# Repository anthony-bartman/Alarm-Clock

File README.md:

# Alarm-Clock
Using Fusion360 and Eagle, I designed an alarm clock circuit board from scratch in my embedded fabrication class

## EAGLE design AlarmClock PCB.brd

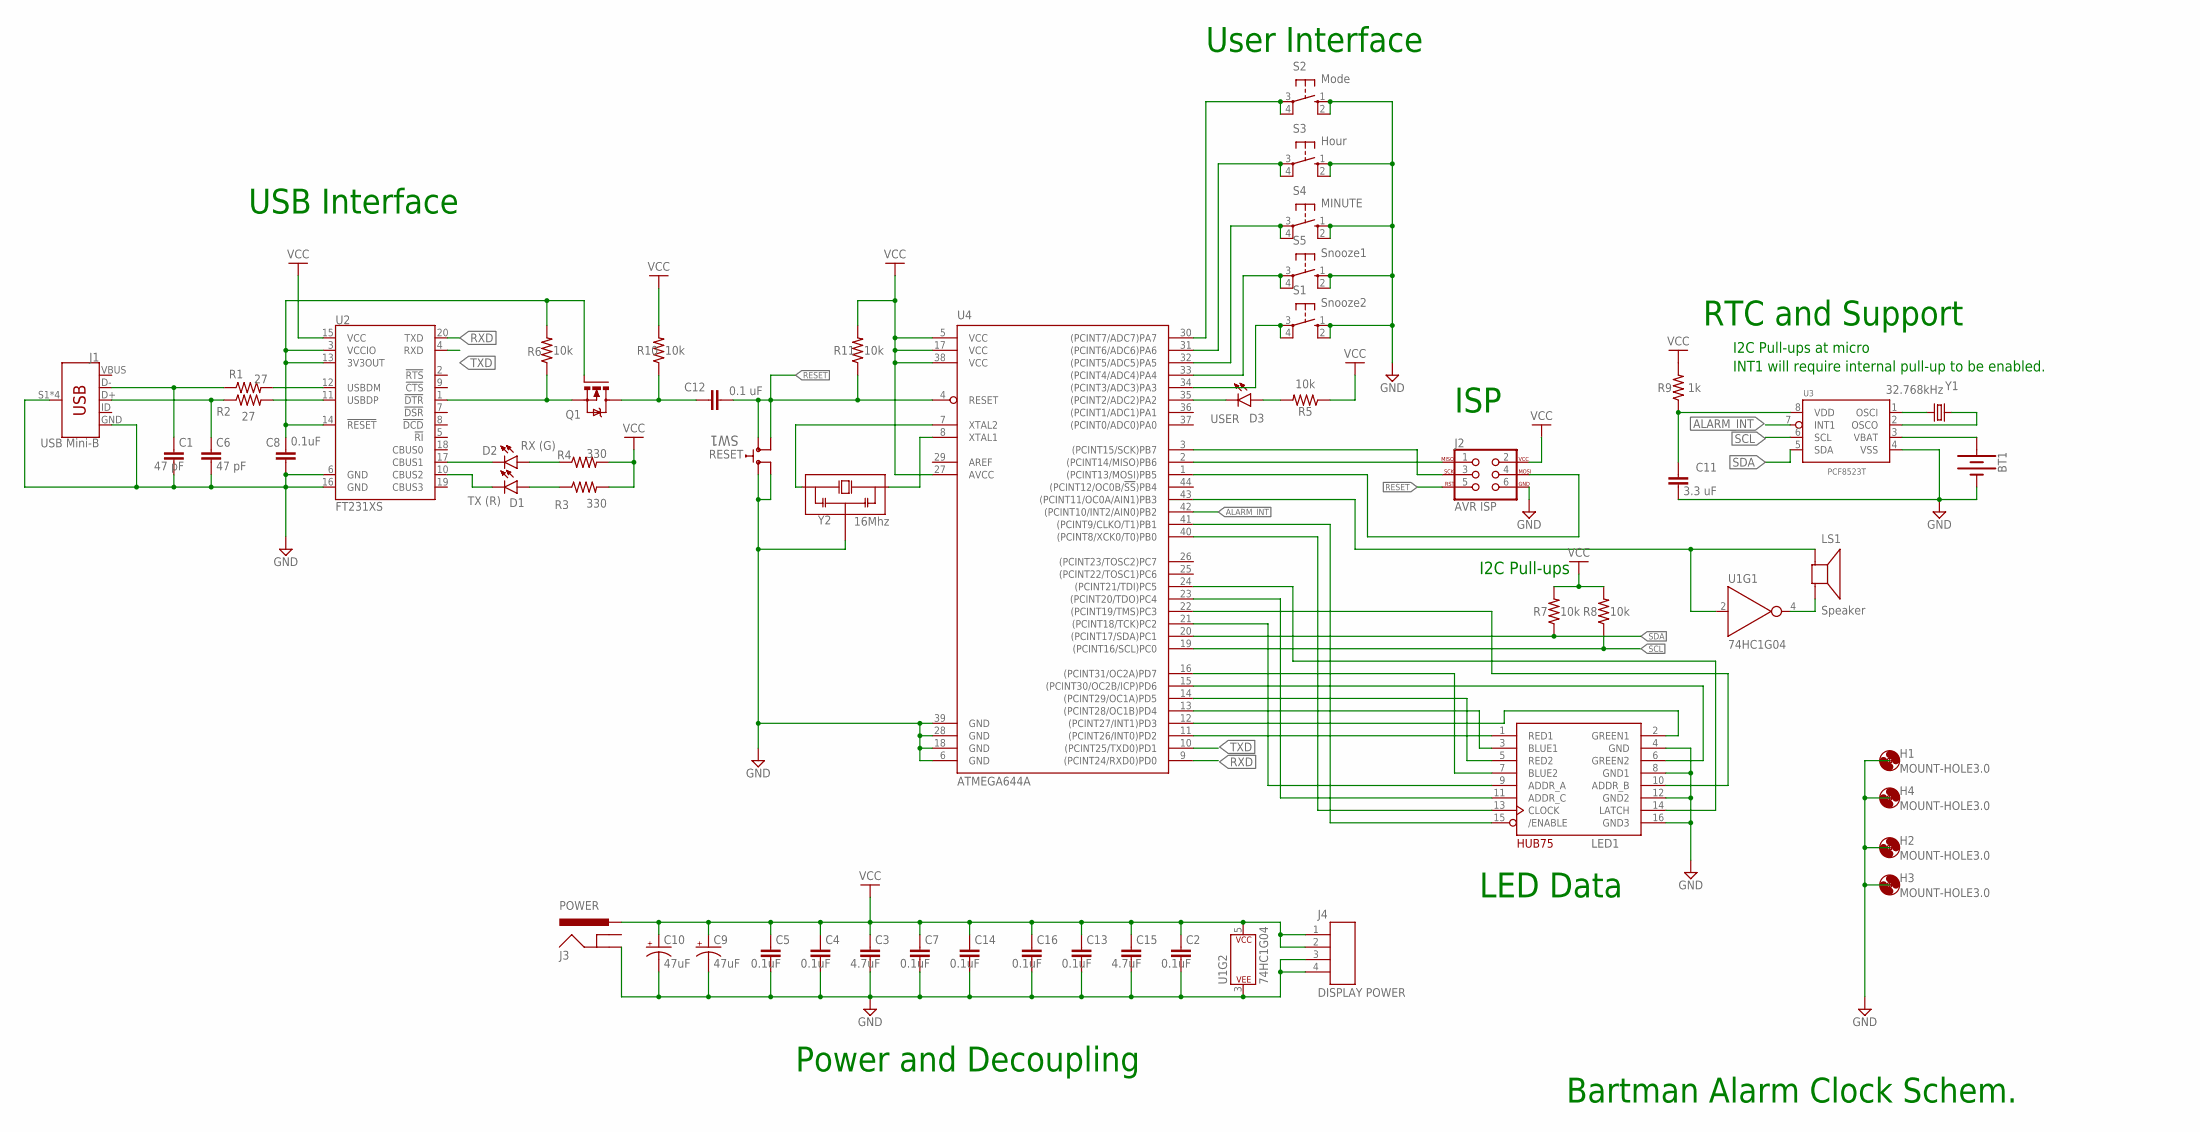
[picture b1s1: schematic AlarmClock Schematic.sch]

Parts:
BT1: BATTERY-20MM_SMD_4LEGS; BATTCON_20MM_4LEGS
C1, C6: 47 pF; CAPC2012X110
C2, C4, C5, C7, C8, C13, C14, C16: 0.1uF; CAPC2012X110
C3, C15: 4.7uF; CAPC2012X110
C9, C10: 47uF; PANASONIC_D
C11: 3.3 uF; CAPC2012X110
C12: 0.1 uF; CAPC2012X110
D1: TX (R); LEDC2012X110N_R
D2: RX (G); LEDC2012X110N_G
D3: USER; LEDC2012X110N_R
H1, H2, H3, H4: MOUNT-HOLE3.0; 3,0
J1: USB Mini-B; USB-MINIB
J2: AVR ISP; 2X3
J3: POWER; POWER_JACK_PTH_BREAD
J4: DISPLAY POWER; JST_B4P-VH(LF)(SN)
LED1: HUB75MATRIX; 2X08-IDC
LS1: Speaker; XDCR_CPT-1625-80-SMT-TR
Q1: BSS123; SOT23
R1, R2: 27; RESC2012X65
R3, R4: 330; RESC2012X65
R5, R6, R7, R8, R10, R11: 10k; RESC2012X65
R9: 1k; RESC2012X65
S1: Snooze2; B3F-10XX
S2: Mode; B3F-10XX
S3: Hour; B3F-10XX
S4: MINUTE; B3F-10XX
S5: Snooze1; B3F-10XX
SW1: FSM2JSMAA; SWITCH_FSM2JSMAA
U1: 74HC1G04; SOT353
U2: FT231XS; SSOP20_L
U3: PCF8523T; SOT96-1
U4: ATMEGA644A; TQFP44
Y1: 32.768kHz; CRYSTAL-SMD-MC-146
Y2: 16Mhz; CSTNE_3SMD

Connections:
ALARM_INT: U3.7 (INT1), U4.42 ((PCINT10/INT2/AIN0)PB2)
GND: BT1.NEGATIVE (-), C1.2, C2.2, C3.2, C4.2, C5.2, C6.2, C7.2, C8.2, C9.-, C10.-, C11.2, C13.2, C14.2, C15.2, C16.2, J1.GND, J1.S1 (SHIELD), J1.S2 (SHIELD), J1.S3 (SHIELD), J1.S4 (SHIELD), J2.6, J3.GND, J4.3, J4.4, LED1.4 (GND), LED1.8 (GND1), LED1.12 (GND2), LED1.16 (GND3), S1.1 (S), S1.2 (S1), S2.1 (S), S2.2 (S1), S3.1 (S), S3.2 (S1), S4.1 (S), S4.2 (S1), S5.1 (S), S5.2 (S1), SW1.1, SW1.2, U1.3 (P$V-), U2.6 (GND), U2.16 (GND), U3.4 (VSS), U4.6 (GND), U4.18 (GND), U4.28 (GND), U4.39 (GND), Y2.2
unnamed: R1.2, U2.12 (USBDM)
unnamed: R2.2, U2.11 (USBDP)
unnamed: C8.1, Q1.1 (G), R6.2, U2.3 (VCCIO), U2.13 (3V3OUT), U2.14 (!RESET)
unnamed: C6.1, J1.D+, R2.1
unnamed: C1.1, J1.D-, R1.1
unnamed: Q1.2 (S), R6.1, U2.1 (!DTR)
unnamed: D2.2 (A), R4.1
unnamed: U4.7 (XTAL2), Y2.1
unnamed: D2.1 (C), U2.17 (CBUS1)
unnamed: D1.1 (C), U2.10 (CBUS2)
unnamed: C12.1, Q1.3 (D), R10.1
unnamed: S2.3, S2.4 (P1), U4.30 ((PCINT7/ADC7)PA7)
unnamed: U4.8 (XTAL1), Y2.3
unnamed: D1.2 (A), R3.1
unnamed: C11.1, R9.1, U3.8 (VDD)
unnamed: BT1.POSITIVE@1 (+), BT1.POSITIVE@2 (+), BT1.POSITIVE@3 (+), BT1.POSITIVE@4 (+), U3.3 (VBAT)
unnamed: U3.1 (OSCI), Y1.P$1 (2)
unnamed: U3.2 (OSCO), Y1.P$2 (1)
unnamed: J2.1, U4.2 ((PCINT14/MISO)PB6)
unnamed: J2.3, U4.3 ((PCINT15/SCK)PB7)
unnamed: J2.4, U4.1 ((PCINT13/MOSI)PB5)
unnamed: D3.2 (A), R5.2
unnamed: LED1.1 (RED1), U4.11 ((PCINT26/INT0)PD2)
unnamed: D3.1 (C), U4.35 ((PCINT2/ADC2)PA2)
unnamed: LED1.3 (BLUE1), U4.13 ((PCINT28/OC1B)PD4)
unnamed: LED1.5 (RED2), U4.14 ((PCINT29/OC1A)PD5)
unnamed: LED1.7 (BLUE2), U4.16 ((PCINT31/OC2A)PD7)
unnamed: LED1.9 (ADDR_A), U4.21 ((PCINT18/TCK)PC2)
unnamed: LED1.11 (ADDR_C), U4.23 ((PCINT20/TDO)PC4)
unnamed: LED1.13 (CLOCK), U4.40 ((PCINT8/XCK0/T0)PB0)
unnamed: LED1.15 (/ENABLE), U4.41 ((PCINT9/CLKO/T1)PB1)
unnamed: LED1.2 (GREEN1), U4.12 ((PCINT27/INT1)PD3)
unnamed: LED1.6 (GREEN2), U4.15 ((PCINT30/OC2B/ICP)PD6)
unnamed: LED1.14 (LATCH), U4.24 ((PCINT21/TDI)PC5)
unnamed: LED1.10 (ADDR_B), U4.22 ((PCINT19/TMS)PC3)
unnamed: LS1.N, U1.4 (Y)
unnamed: LS1.P, U1.2 (A), U4.43 ((PCINT11/OC0A/AIN1)PB3)
unnamed: S5.3, S5.4 (P1), U4.33 ((PCINT4/ADC4)PA4)
unnamed: S3.3, S3.4 (P1), U4.31 ((PCINT6/ADC6)PA6)
unnamed: S4.3, S4.4 (P1), U4.32 ((PCINT5/ADC5)PA5)
unnamed: S1.3, S1.4 (P1), U4.34 ((PCINT3/ADC3)PA3)
RESET: C12.2, J2.5, R11.1, SW1.3, SW1.4, U4.4 (RESET)
RXD: U2.20 (TXD), U4.9 ((PCINT24/RXD0)PD0)
SCL: R8.1, U3.6 (SCL), U4.19 ((PCINT16/SCL)PC0)
SDA: R7.1, U3.5 (SDA), U4.20 ((PCINT17/SDA)PC1)
TXD: U2.4 (RXD), U4.10 ((PCINT25/TXD0)PD1)
VBUS: J1.VBUS
VCC: C2.1, C3.1, C4.1, C5.1, C7.1, C9.+, C10.+, C13.1, C14.1, C15.1, C16.1, J2.2, J3.PWR, J4.1, J4.2, R3.2, R4.2, R5.1, R7.2, R8.2, R9.2, R10.2, R11.2, U1.5 (P$V+), U2.15 (VCC), U4.5 (VCC), U4.17 (VCC), U4.27 (AVCC), U4.38 (VCC)

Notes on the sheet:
I2C Pull-ups
LED Data
User Interface
Power and Decoupling
USB Interface
Bartman Alarm Clock Schem.
ISP
I2C Pull-ups at micro
INT1 will require internal pull-up to be enabled.
RTC and Support

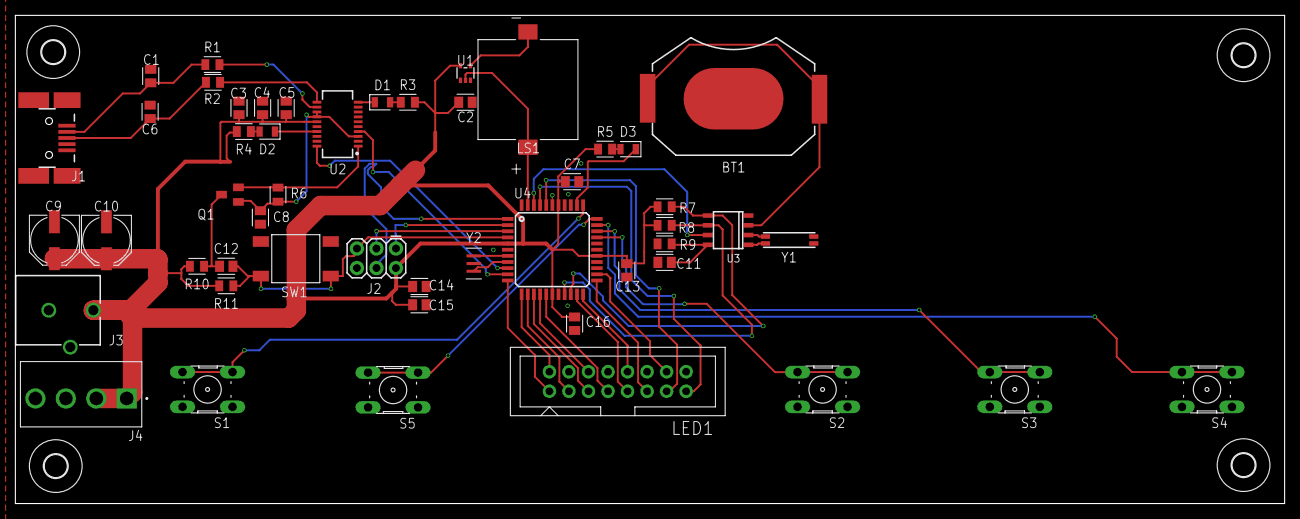
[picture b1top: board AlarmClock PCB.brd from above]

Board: 2 copper layers, 165.1 x 63.5 mm, 54 parts (0 on the bottom side), 49 nets.

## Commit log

2021-03-18 Adding Alarm Clock Files

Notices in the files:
parts and their libraries:
SparkFun-Batteries: Licensing: Creative Commons ShareAlike 4.0 International - https://creativecommons.org/licenses/by-sa/4.0
